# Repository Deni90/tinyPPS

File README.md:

## Description

TinyPPS is a pocket-sized programmable power supply built on the USB Power Delivery (PD) standard and the USB Programmable Power Supply (PPS) feature. It transforms a standard USB-C PD charger into a flexible bench-style power source by negotiating selectable output voltages and current limits directly with the charger.

## Key features

TinyPPS takes advantage of pin-compatible USB PD sink ICs (AP33772 and AP33772S), providing two feature sets within a single firmware, depending on the selected IC:

| Feature | With AP33772s | With AP33772 |
| - | - | - |
| Supported PDO profiles | fixed PDO, PPS | fixed PDO, PPS |
| Output voltage range | 3.3 - 21V | 3.3 - 21V |
| Max output current* | 5A | 5A |
| PPS voltage step size | 100mV/Step | 20mV/Step |
| Programmable current limit | 250mA/Step | 50mA/Step |
| User-switchable output | ✅ | ✅ |
| Over Voltage Protection (OVP) | ✅ → Hard Reset and Auto Restart | ✅ → Auto Restart |
| Over Current Protection (OCP) | ✅ → Output Disable | ✅ → Auto Restart |
| Under Voltage Protection (UVP) | ✅ → Output Disable | ❌ |
| Over temperature protection (OTP)** | ✅ → Output Disable | ✅ → Output Disable |
| Short-Circuit Protection (SCP) | ✅ → Output Disable | ✅ → Output Disable |

**charger and cable dependent*

***OTP is set to 85°C*

Huge thank you to **[PCBWay](https://www.pcbway.com)** for sponsoring this project!

## Firmware

The firmware is written in C++ using the Raspberry Pi Pico SDK. No external dependencies are used.

Configuring the build using CMake:

```bash
cd firmware
cmake -G Ninja -S . -B build
```

Building the firmware:

```bash
cmake --build build
```

## Flashing

There are two options to flash RP2040:
1. Via USB by pressing the `BOOT` button during power on. On a PC a new virtual drive called `RPI-RP2` should appear. Then, drag and drop a *.uf2* file onto the drive.
2. Via SWD interface by attaching a debugger like Raspberry Pi Debug Probe to the "DBG" connector and then using OpenOCD.
    ```bash
    cmake --build build --target flash
    ```

## Hardware

Schematic and PCB are designed in KiCAD 10.

Key components:

- The device is based on the **RP2040** microcontroller and **AP33772(S)** USB PD sink controller.
- A **0.96 in 128×64 SSD1306 OLED** is added to display the UI.
- A **EC11** rotary encoder is added for user input.
- **INA226** is used for measuring current and voltage. *While AP33772s provides these features, INA226 gives more precise measurements.*
- **LM73100** replaces the back-to-back NMOS switch and provides short circuit protection.
- **74LVC1G08GW,125** single 2-input AND gate is used for output enable.

## Case

3D model is made with Autodesk Fusion 360.

The case is 3D printed with ABS so it can handle higher tempeatures.

## Resources

1. [Hardware design with RP2040](https://pip-assets.raspberrypi.com/categories/814-rp2040/documents/RP-008279-DS-1-hardware-design-with-rp2040.pdf?disposition=inline)
2. [AP33772S I2C USB PD Sink Controller EVB User Guide](https://www.diodes.com/assets/Evaluation-Boards/AP33772S-Sink-Controller-EVB-User-Guide.pdf)
3. [SSD1306](https://cdn-shop.adafruit.com/datasheets/SSD1306.pdf)
4. [INA226](https://www.ti.com/lit/ds/symlink/ina226.pdf?ts=1770072845830)

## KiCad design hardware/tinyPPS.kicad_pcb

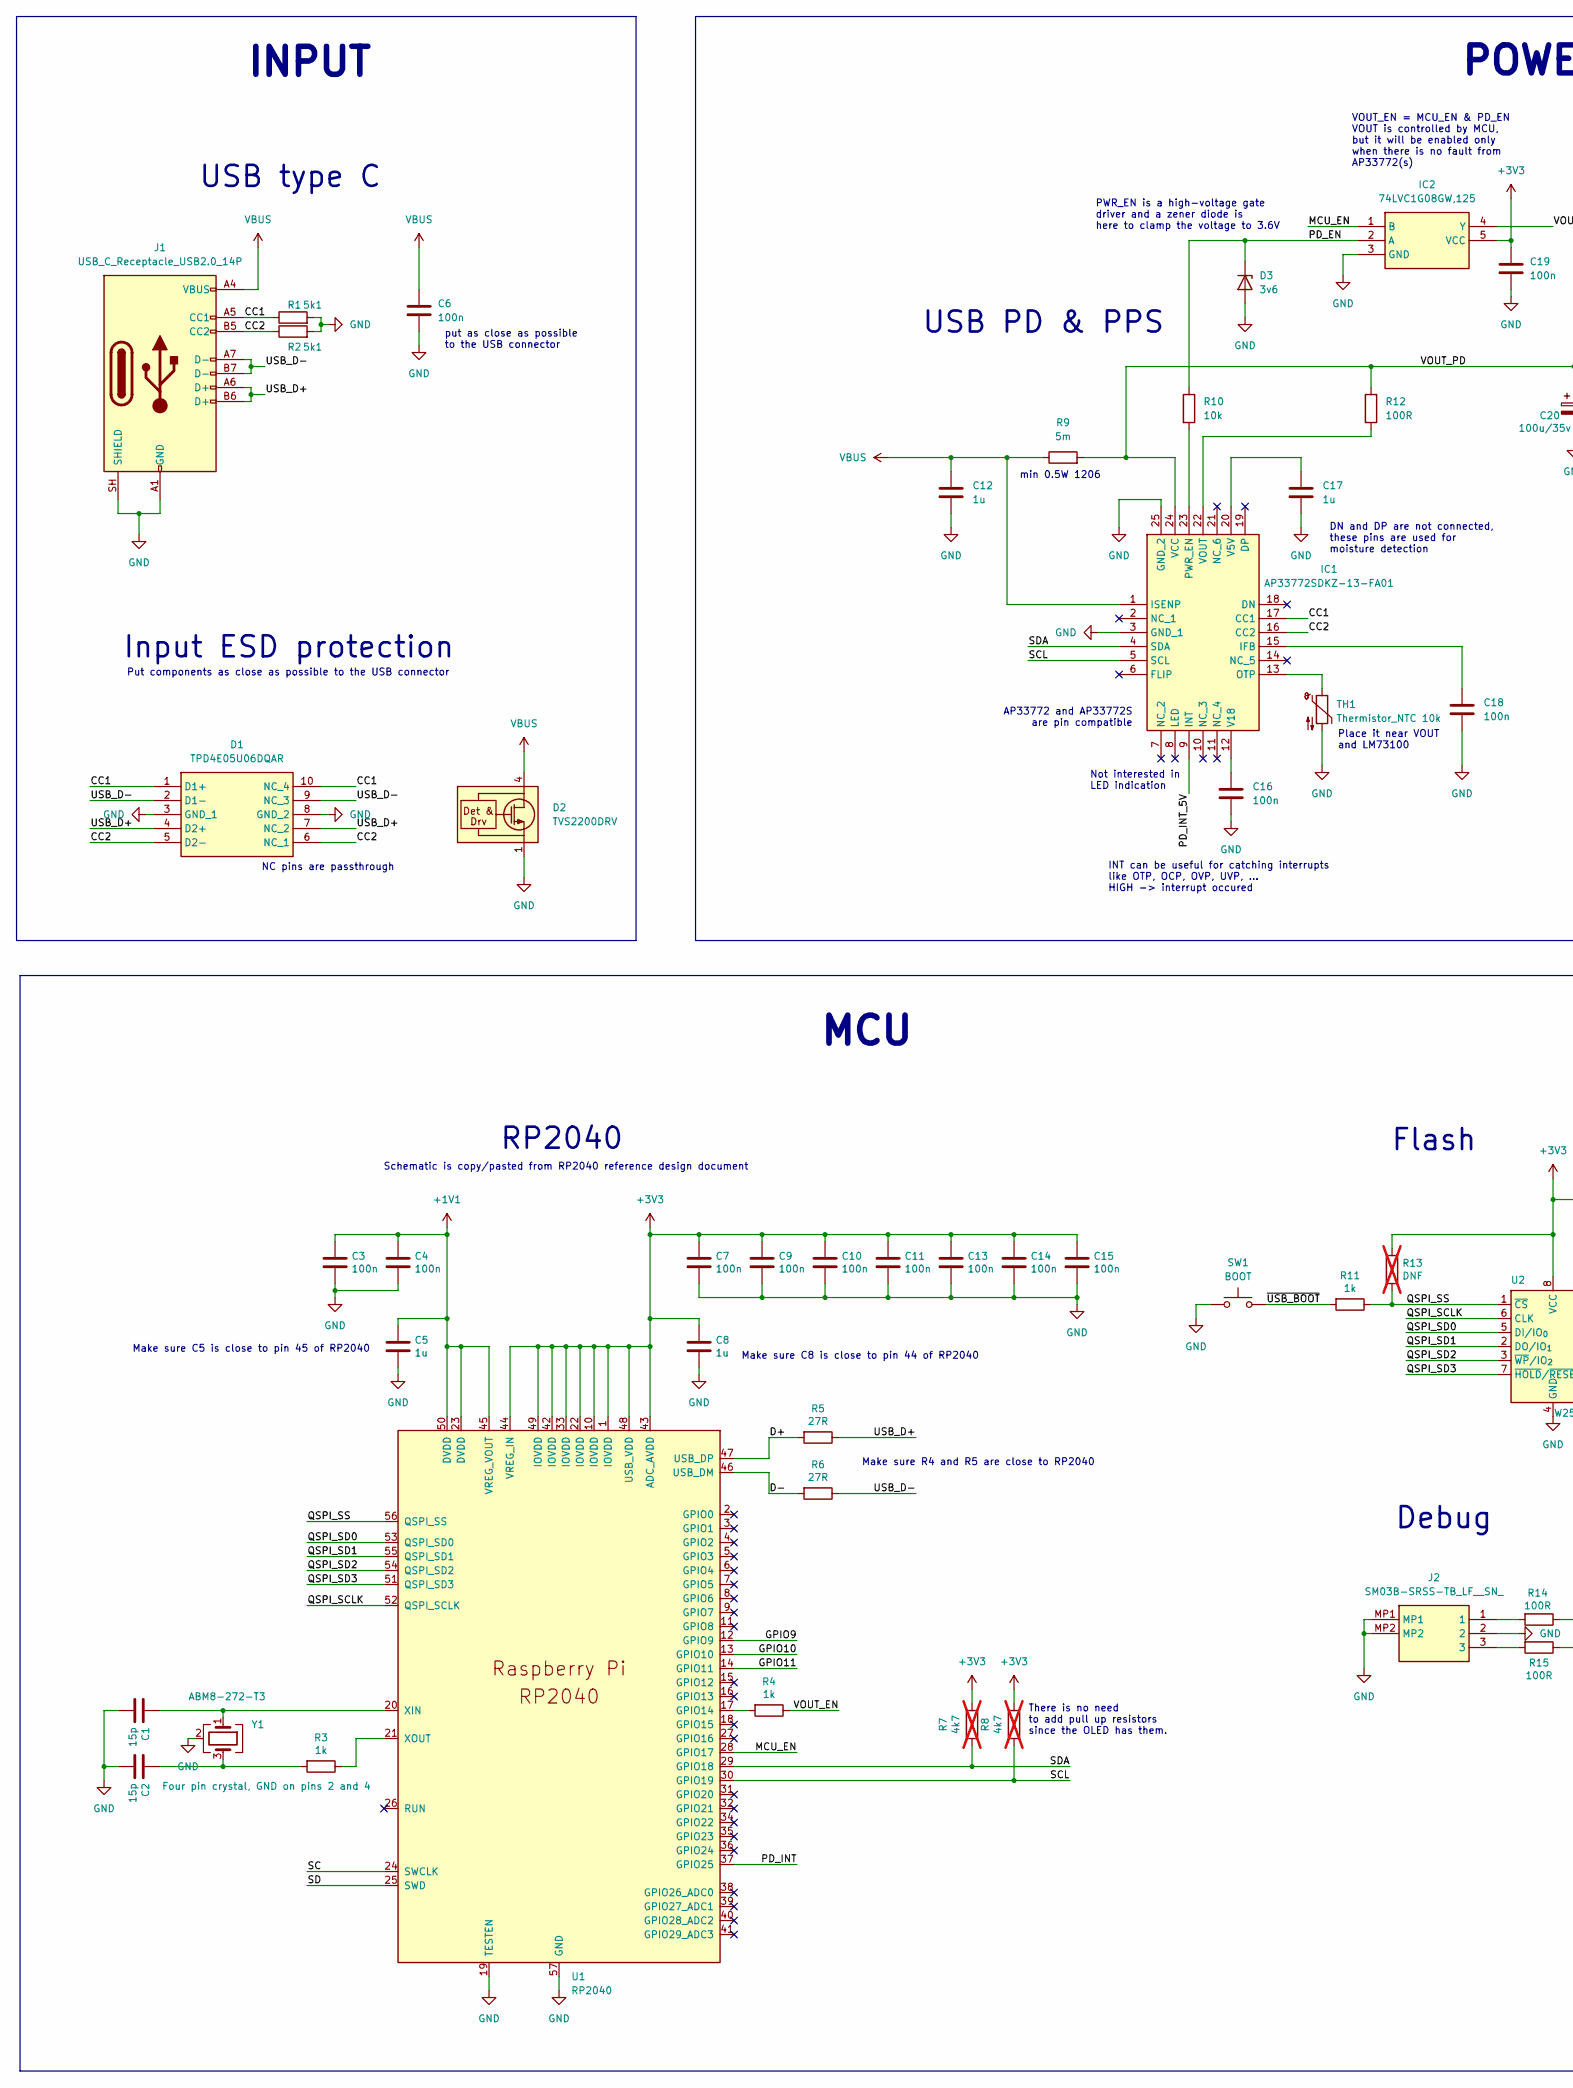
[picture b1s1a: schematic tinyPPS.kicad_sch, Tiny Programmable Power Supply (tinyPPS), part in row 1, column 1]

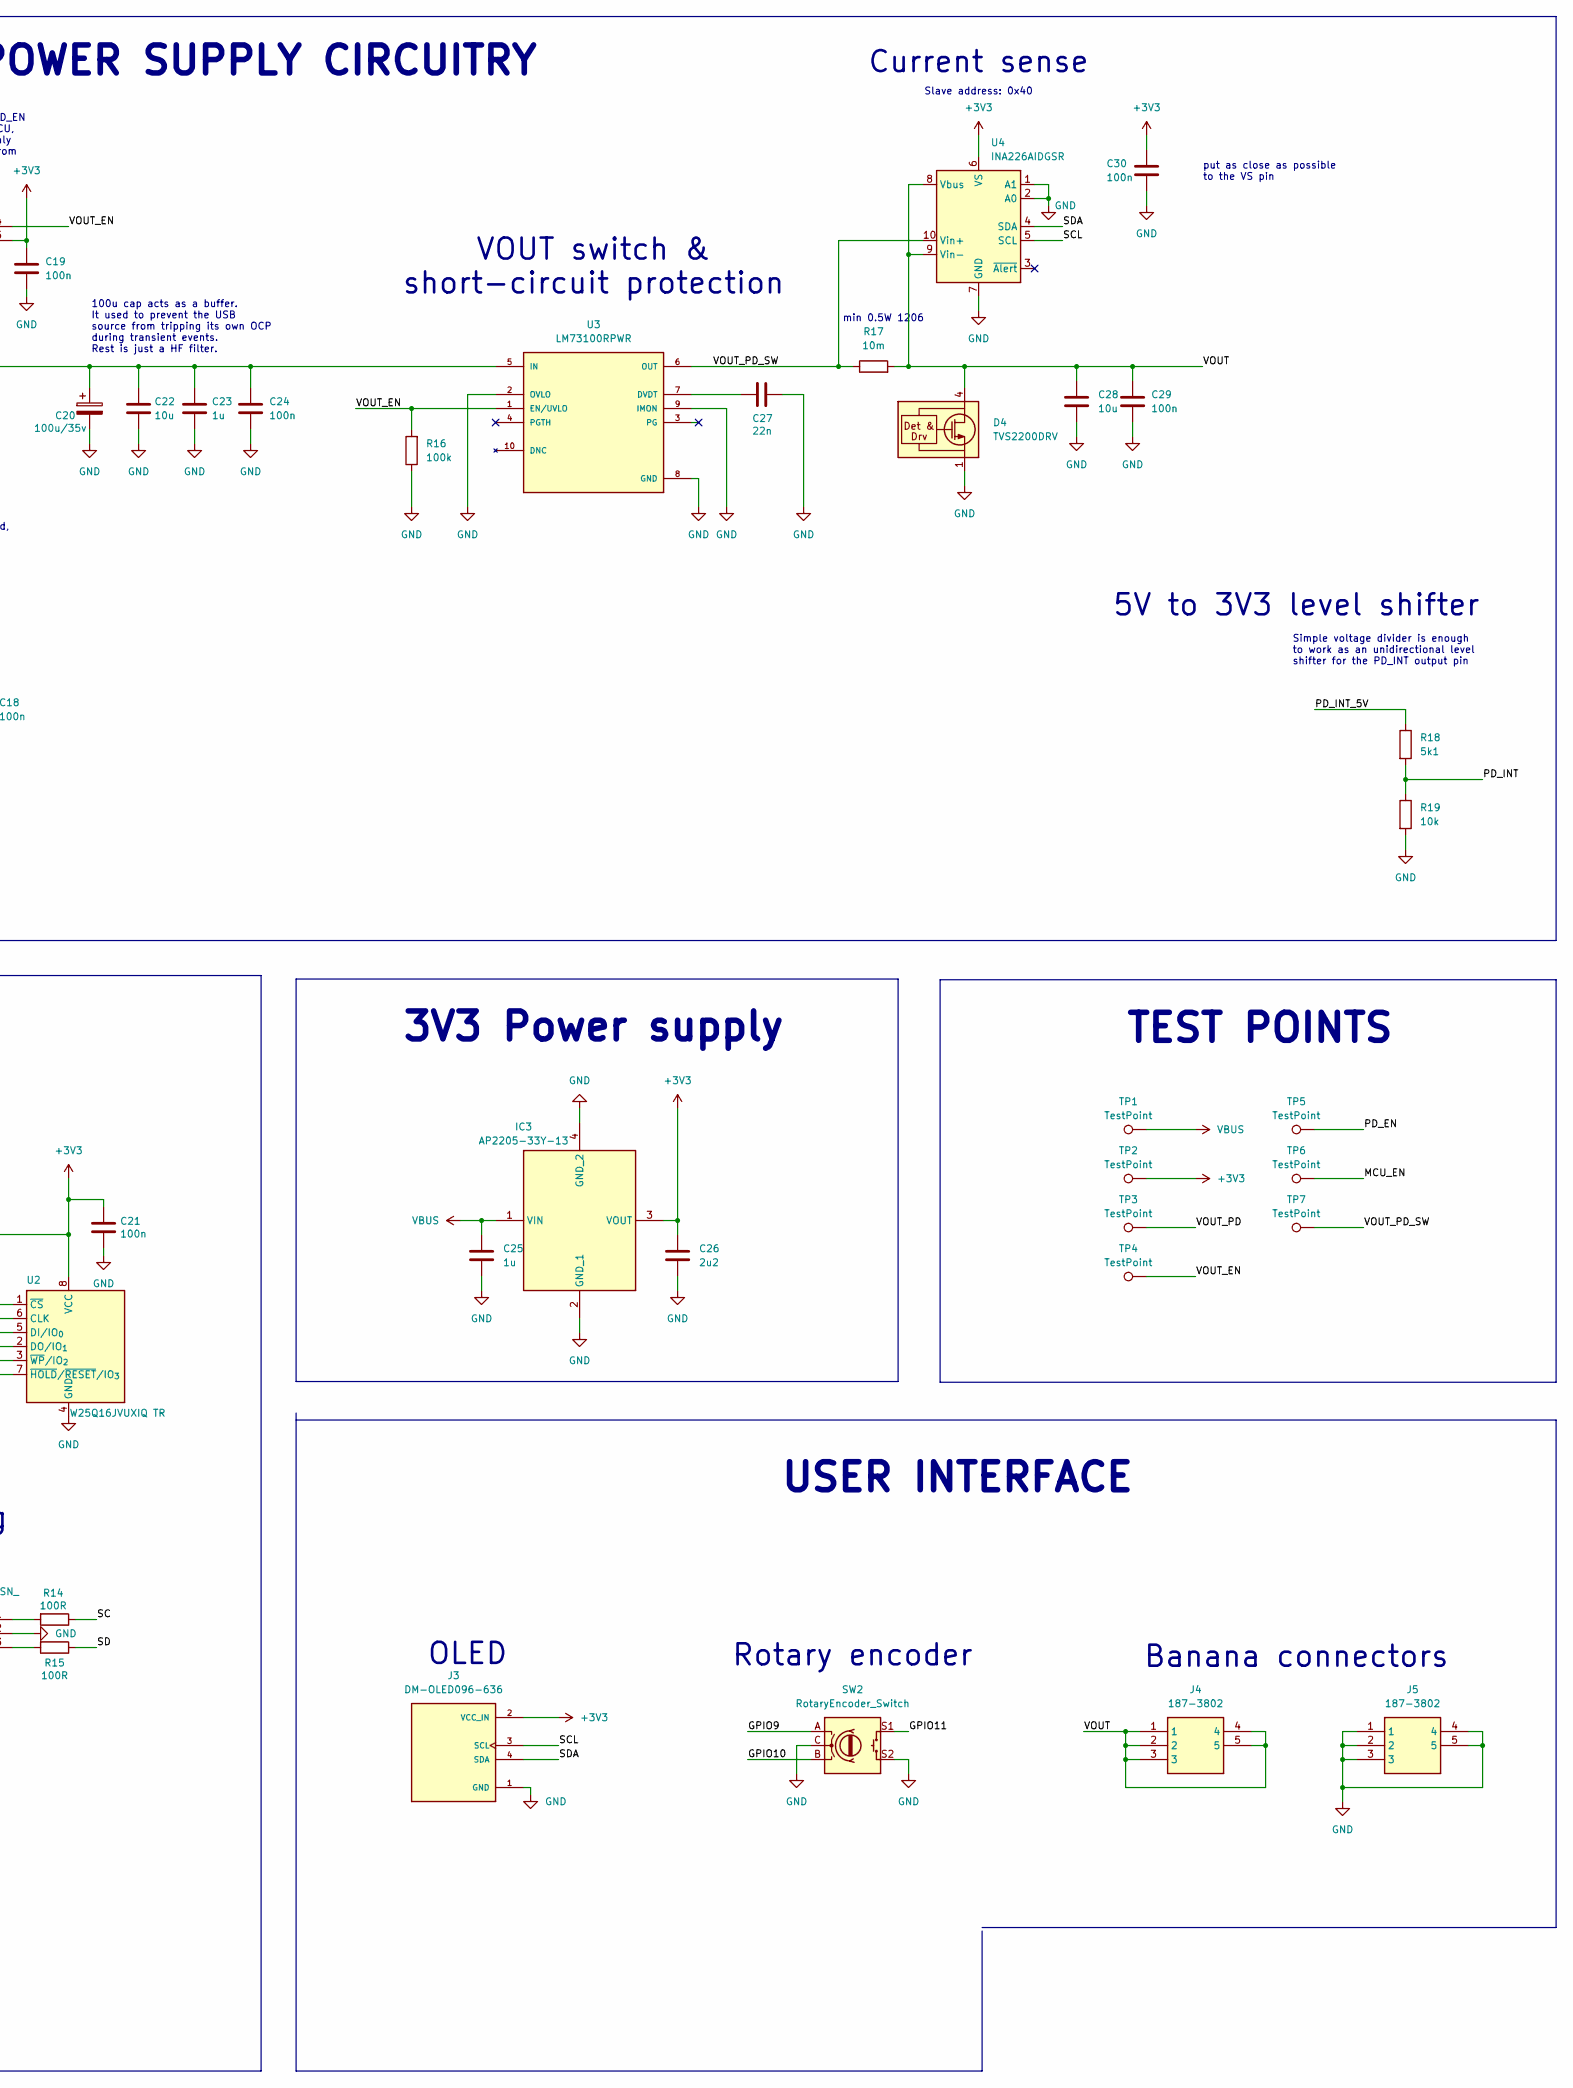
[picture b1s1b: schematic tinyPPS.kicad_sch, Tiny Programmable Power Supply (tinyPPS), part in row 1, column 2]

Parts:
C1, C2: 15p; C_0402_1005Metric
C3, C4, C6, C7, C9, C10, C11, C13, C14, C15, C16, C18, C19, C21, C24, C29, C30: 100n; C_0402_1005Metric
C5, C8, C12, C17, C25: 1u; C_0402_1005Metric
C20: 100u/35v; CP_Elec_6.3x7.7
C22, C28: 10u; C_0805_2012Metric
C23: 1u; C_0805_2012Metric
C26: 2u2; C_0402_1005Metric
C27: 22n; C_0402_1005Metric
D1: TPD4E05U06DQAR; DQA_R-PUSON-N10_; Mouser Part Number 595-TPD4E05U06DQAR
D2, D4: TVS2200DRV; WSON-6-1EP_2x2mm_P0.65mm_EP1x1.6mm
D3: 3v6; D_SOD-323
IC1: AP33772SDKZ-13-FA01; AP33772SDKZ13FA01; Mouser Part Number 621-P33772SDKZ13FA01
IC2: 74LVC1G08GW,125; SOT65P210X110-5N; Mouser Part Number 771-74LVC1G08GW-G
IC3: AP2205-33Y-13; 2DB1132R13; Mouser Part Number 621-AP2205-33Y-13
J1: USB_C_Receptacle_USB2.0_14P; USB_C_Receptacle_GCT_USB4105-xx-A_16P_TopMnt_Horizontal
J2: SM03B-SRSS-TB_LF__SN_; SM03BSRSSTBLFSN; Mouser Part Number N/A
J3: DM-OLED096-636; MODULE_DM-OLED096-636; PARTREV 2018-09-10
J4, J5: 187-3802; 1873802; Manufacturer_Part_Number 187-3802
R1, R2, R18: 5k1; R_0402_1005Metric
R3, R4, R11: 1k; R_0402_1005Metric
R5, R6: 27R; R_0402_1005Metric
R7, R8: 4k7; R_0402_1005Metric; not fitted
R9: 5m; R_1206_3216Metric
R10, R19: 10k; R_0402_1005Metric
R12, R14, R15: 100R; R_0402_1005Metric
R13: DNF; R_0402_1005Metric; not fitted
R16: 100k; R_0402_1005Metric
R17: 10m; R_1206_3216Metric
SW1: BOOT; SW_3x4mm
SW2: RotaryEncoder_Switch; EC11 horizontal
TH1: Thermistor_NTC 10k; R_0402_1005Metric
TP1, TP2, TP3, TP4, TP5, TP6, TP7: TestPoint; TestPoint_Pad_D1.0mm
U1: RP2040; RP2040-QFN-56
U2: W25Q16JVUXIQ TR; Winbond_USON-8-1EP_3x2mm_P0.5mm_EP0.2x1.6mm
U3: LM73100RPWR; IC_LM73100RPWR; PARTREV 08/2019
U4: INA226AIDGSR; TSSOP-10_3x3mm_P0.5mm
Y1: ABM8-272-T3; Crystal_SMD_3225-4Pin_3.2x2.5mm

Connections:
+1V1: C3.1, C4.1, C5.1, U1.23 (DVDD), U1.45 (VREG_VOUT), U1.50 (DVDD)
+3V3: C7.1, C8.1, C9.1, C10.1, C11.1, C13.1, C14.1, C15.1, C19.1, C21.1, C26.1, C30.1, IC2.5 (VCC), IC3.3 (VOUT), J3.2 (VCC_IN), R7.1, R8.1, R13.1, TP2.1 (1_1), U1.1 (IOVDD), U1.10 (IOVDD), U1.22 (IOVDD), U1.33 (IOVDD), U1.42 (IOVDD), U1.43 (ADC_AVDD), U1.44 (VREG_IN), U1.48 (USB_VDD), U1.49 (IOVDD), U2.8 (VCC), U4.6 (VS)
/CC1: D1.1 (D1+), D1.10 (NC_4), IC1.17 (CC1), J1.A5 (CC1), R1.1
/CC2: D1.5 (D2-), D1.6 (NC_1), IC1.16 (CC2), J1.B5 (CC2), R2.1
/D+: R5.2, U1.47 (USB_DP)
/D-: R6.2, U1.46 (USB_DM)
/GPIO9: SW2.A, U1.12 (GPIO9)
/GPIO10: SW2.B, U1.13 (GPIO10)
/GPIO11: SW2.S1, U1.14 (GPIO11)
/MCU_EN: IC2.1 (B), TP6.1 (1_1), U1.28 (GPIO17)
/PD_EN: D3.1 (K), IC2.2 (A), R10.1, TP5.1 (1_1)
/PD_INT: R18.2, R19.1, U1.37 (GPIO25)
/PD_INT_5V: IC1.9 (INT), R18.1
/QSPI_SCLK: U1.52 (QSPI_SCLK), U2.6 (CLK)
/QSPI_SD0: U1.53 (QSPI_SD0), U2.5 (DI/IO_{0})
/QSPI_SD1: U1.55 (QSPI_SD1), U2.2 (DO/IO_{1})
/QSPI_SD2: U1.54 (QSPI_SD2), U2.3 (~WP/IO_{2})
/QSPI_SD3: U1.51 (QSPI_SD3), U2.7 (~HOLD/~RESET/IO_{3})
/QSPI_SS: R11.1, R13.2, U1.56 (QSPI_SS), U2.1 (~CS)
/SC: R14.1, U1.24 (SWCLK)
/SCL: IC1.5 (SCL), J3.3 (SCL), R8.2, U1.30 (GPIO19), U4.5 (SCL)
/SD: R15.1, U1.25 (SWD)
/SDA: IC1.4 (SDA), J3.4 (SDA), R7.2, U1.29 (GPIO18), U4.4 (SDA)
/USB_D+: D1.4 (D2+), D1.7 (NC_2), J1.A6 (D+), J1.B6 (D+), R5.1
/USB_D-: D1.2 (D1-), D1.9 (NC_3), J1.A7 (D-), J1.B7 (D-), R6.1
/VOUT: C28.1, C29.1, D4.4 (IN), D4.5 (IN), D4.6 (IN), J4.1, J4.2, J4.3, J4.4, J4.5, R17.2, U4.8 (Vbus), U4.9 (Vin-)
/VOUT_EN: IC2.4 (Y), R4.1, R16.2, TP4.1 (1_1), U3.1 (EN/UVLO)
/VOUT_PD: C20.1, C22.1, C23.1, C24.1, IC1.24 (VCC), R9.2, R12.2, TP3.1 (1_1), U3.5 (IN)
/VOUT_PD_SW: R17.1, TP7.1 (1_1), U3.6 (OUT), U4.10 (Vin+)
/~USB_BOOT: R11.2, SW1.2
GND: C1.2, C2.2, C3.2, C4.2, C5.2, C6.2, C7.2, C8.2, C9.2, C10.2, C11.2, C12.2, C13.2, C14.2, C15.2, C16.2, C17.2, C18.2, C19.2, C20.2, C21.2, C22.2, C23.2, C24.2, C25.2, C26.2, C27.2, C28.2, C29.2, C30.2, D1.3 (GND_1), D1.8 (GND_2), D2.1 (GND), D2.2 (GND), D2.3 (GND), D2.7 (GND), D3.2 (A), D4.1 (GND), D4.2 (GND), D4.3 (GND), D4.7 (GND), IC1.3 (GND_1), IC1.25 (GND_2), IC2.3 (GND), IC3.2 (GND_1), IC3.4 (GND_2), J1.A1 (GND), J1.A12 (GND), J1.B1 (GND), J1.B12 (GND), J1.SH (SHIELD), J2.2, J2.MP1, J2.MP2, J3.1 (GND), J5.1, J5.2, J5.3, J5.4, J5.5, R1.2, R2.2, R16.1, R19.2, SW1.1, SW2.C, SW2.S2, TH1.2, U1.19 (TESTEN), U1.57 (GND), U2.4 (GND), U3.2 (OVLO), U3.8 (GND), U3.9 (IMON), U4.1 (A1), U4.2 (A0), U4.7 (GND), Y1.2 (G), Y1.4 (G)
unnamed: C2.1, R3.2, Y1.3
unnamed: C18.1, IC1.15 (IFB)
unnamed: IC1.13 (OTP), TH1.1
unnamed: IC1.23 (PWR_EN), R10.2
unnamed: C17.1, IC1.20 (V5V)
unnamed: C16.1, IC1.12 (V18)
unnamed: IC1.22 (VOUT), R12.1
unnamed: J2.1, R14.2
unnamed: J2.3, R15.2
unnamed: R4.2, U1.17 (GPIO14)
unnamed: C1.1, U1.20 (XIN), Y1.1
unnamed: R3.1, U1.21 (XOUT)
unnamed: C27.1, U3.7 (DVDT)
VBUS: C6.1, C12.1, C25.1, D2.4 (IN), D2.5 (IN), D2.6 (IN), IC1.1 (ISENP), IC3.1 (VIN), J1.A4 (VBUS), J1.A9 (VBUS), J1.B4 (VBUS), J1.B9 (VBUS), R9.1, TP1.1 (1_1)

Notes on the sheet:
100u cap acts as a buffer. It used to prevent the USB source from tripping its own OCP during transient events. Rest is just a HF filter.
There is no need to add pull up resistors since the OLED has them.
AP33772 and AP33772S are pin compatible
min 0.5W 1206
MCU
Not interested in LED indication
VOUT_EN = MCU_EN & PD_EN VOUT is controlled by MCU, but it will be enabled only when there is no fault from AP33772(s)
DN and DP are not connected, these pins are used for moisture detection
INPUT
Debug
put as close as possible to the USB connector
Input ESD protection
VOUT switch & short-circuit protection
Banana connectors
OLED
Slave address: 0x40
USB PD & PPS
Place it near VOUT and LM73100
Make sure R4 and R5 are close to RP2040
Flash
3V3 Power supply
INT can be useful for catching interrupts like OTP, OCP, OVP, UVP, ... HIGH -> interrupt occured
Make sure C5 is close to pin 45 of RP2040
Schematic is copy/pasted from RP2040 reference design document
put as close as possible to the VS pin
Make sure C8 is close to pin 44 of RP2040
USER INTERFACE
NC pins are passthrough
RP2040
Current sense
Rotary encoder
POWER SUPPLY CIRCUITRY
TEST POINTS
PWR_EN is a high-voltage gate driver and a zener diode is here to clamp the voltage to 3.6V
5V to 3V3 level shifter
USB type C
Simple voltage divider is enough to work as an unidirectional level shifter for the PD_INT output pin
Put components as close as possible to the USB connector

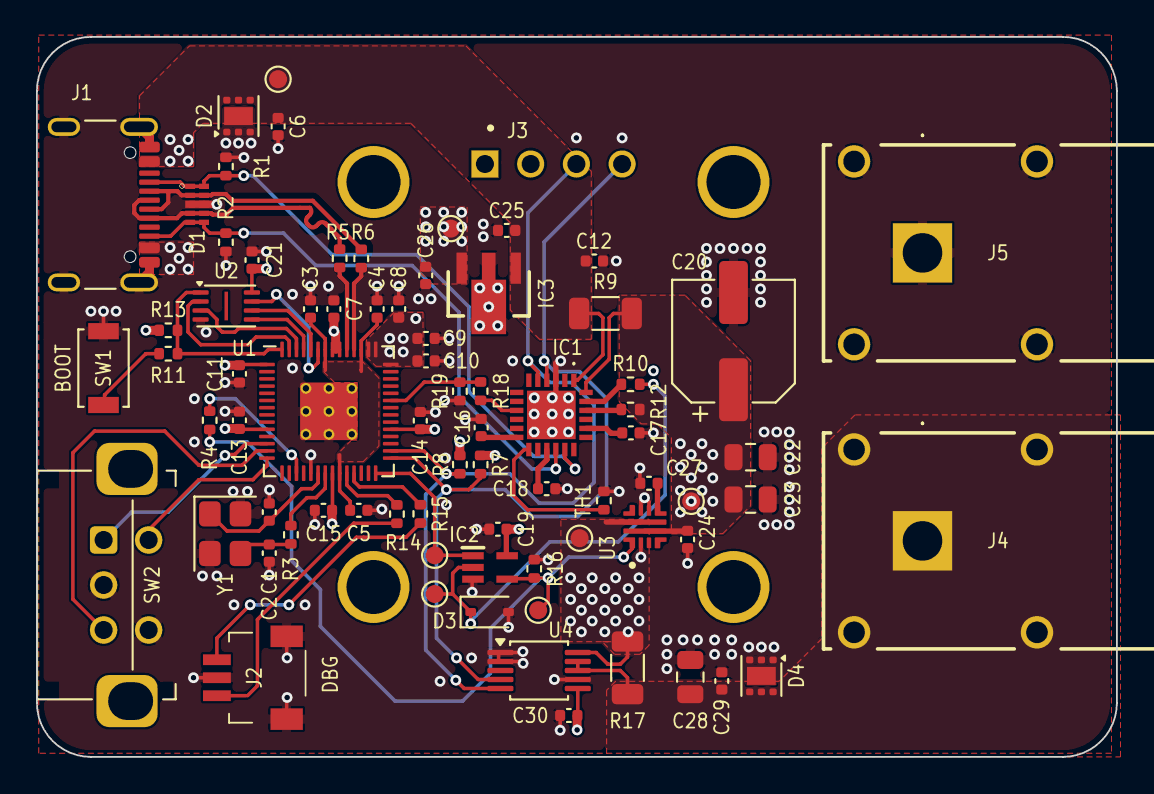
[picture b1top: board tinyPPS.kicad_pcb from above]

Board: 4 copper layers, 60.0 x 40.0 mm, 76 parts (0 on the bottom side), 45 nets.

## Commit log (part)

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2025-05-25 Implement a basic TinyPPS GUI layout and control
    - Implement OLED display driver
    - Implement rotary encoder driver
    - Implement main menu and main screens
    - Handle rotary encoder states
2025-06-03 Add schematic & PCB
2025-08-05 Update function names in ssd1306 to match the coding style
2025-08-11 Remove LED connection and update PD_INT level shifter
2025-08-12 Use back-to-back N MOS switch with common source
2025-08-12 Replace led indicator with mode
2025-08-13 Update project name in CMake
2025-08-13 Extend TinyPPS with initialize function
2025-08-18 Change rotary encoder to a horizontal type
    - Re-route the PCB
    - Make PCB with smaller (60mm)
2025-08-23 Update PCB routing - use +3v3 and GND planes
2025-08-29 Change PCB size to 60x40mm and update INA226 circuit
2025-12-03 Change footprint for flash to WSON-8 6x5mm and re-route the PCB
2026-01-21 Use rp2040, update GPIOs and INA226 shunt value to match PCB
2026-01-21 rotary_encoder: Move init to a separate function
2026-01-21 rp_imp: Move i2c initialization to separate function
2026-01-21 Show loading screen at startup
2026-01-24 Fix reading current from INA226
    - Remove output filterfing from INA266, cause it may not be correctly
    implemented.
2026-01-25 Update menu and loading screens to use simply "PDO" as term
2026-01-25 Read and show the number of PDOs from AP33772s
    - Add an app33772s module used for the driver code
    - Define register objects (Status, Mask, System, SrcPdo and PdReqMsg)
    - Implement a basic API for getting status, setting NTC values, control the
    ouput enable NMOS switch and read PDOs from a USB power source.
2026-01-26 Move config* to utils folder
2026-01-28 Move PdoType enum to Ap33772s class
2026-01-28 Show menu only if enabled and when the output is turned off
2026-01-28 Implement PDO selection
    - Extend Ap33772s with setVselMin function to enable voltages bellow 5V.
    - Extend Ap33772s with getPdo funtion for retrieving PDO at specified index.
    - Extend Ap33772s with setPdoOutput function for selecting PDO with output
    voltage and current.
    - Update config to use Pdo structure.
    - Integrate PDO selection into main module.
2026-01-29 Ap33772s: Add helper functions for i2c handling
2026-01-29 MainScreen: Convert temperature member to int
2026-01-29 Disable warnings caused by using std::format
2026-01-29 Fix showing default target V for a when there is no PDO available
    The issue is fixed by setting voltage_min to 5000 in Pdo's constructor.
2026-01-29 MainScreen: Calculate the x position for target current/voltage strings
2026-01-30 Ap33772s: Expose getStatus and setMask functions to public API
2026-01-30 Hal: rename pin_iface to gpio_iface
2026-01-30 Hal: Simplify initialization of gpio pins
    - Add Direction and Pull enums
    - Move GPIO init to a configure function
2026-01-30 Hal: Move timer stuff to HAL and implement a PicoRepeatingTimer
2026-01-31 TinyPPS: Move output_enable under TinyPPS class
2026-01-31 Gui: Add logo to loading screen
2026-02-02 Gpio: Add interrupt handling to the API
2026-02-02 Handle faults triggered by the PD_INT interrupt
    - Attach an interrupt to PD_INT pin
    - Disable output if fault is raised
2026-02-07 TinyPPS: Add init state to State enum
    - Move readPDO to handleInitState function
2026-02-07 Ap33772s: Remove non-working code from getPdo
2026-02-07 Gui: MainScreen - use "LIMIT" text for current
2026-03-26 Update README fix values for output voltage range
2026-04-01 Gui: MenuScreen - Fix showing all menu items properly
    Decrease max_menu_size by one to match the layout height. This solves the
    problem of showing the 7th menu item on the next page.
2026-04-27 TinyPPS: Remove i2c handling from ISR
    ISR now only sets an interrupt flag. I2C read is handled in main state.
2026-04-27 Ap33772s: Move i2c address to classes public section
2026-04-27 TinyPPS: Declare m_is_fault_detected as volatile
2026-04-27 HAL: Extend HAL with IPdSink for USB PD Sink control
    IPdSink class provides a generic API for USB Power Delivery Sink hardware. This
    addition opens the possibility to support different types of PD controllers
    without modifying code in the main module.
2026-04-27 Ap33772s: Refactor the module by implementing the IPdSink interface
    Refactor Ap33772s to use IPdSink interface and update other modules to use
    objects from IPdSink.
2026-04-27 PCB: Assign colors to nets to improve readability
2026-04-27 Hardware: Switch to 4-layer board setup
    Schematic:
    - Add TVS diodes to input and output
    - Support both AP33772 and AP33772s
    - Replace back-to-back NMOS swith with a single LM73100. AP33772(s) has a
    PWR_EN pin that is used as a gate driver for the NMOS switch. Voltage levels
    of the PWR_EN can be greater than the maximum rating of 6.5V for LM73100.
2026-04-27 TinyPPS: Add support for AP33772
    - Implement an AP33772 module based on IPdSink
    - Integrate AP33772 to TinyPPS
    - Extend probe function to detect AP33772 by default and fallback to AP33772s
    if it is not detected
2026-05-24 Hal: Modernize code and address clang-tidy warnings
    - Use a trailing return type for functions
    - Rename cb parameter to callback
2026-05-24 PicoHal:: Fix clang-tidy warnings
    - Modernize C++ code
    - Use better variable/argument names
2026-05-24 Ina226: Fix clang-tidy warnings
    - Modernize C++ code
2026-05-24 RotaryEncoder: Fix clang-tidy warnings
    - Modernize C++ code
2026-05-25 Ap33772(s): Fix clang-tidy warnings
    - Modernize C++ code
2026-05-25 TinyPPS: Modernize C++ code
2026-05-25 RotaryEncoder: Refactor Handle() function
    - Move static variables from Handle() to class members to enable proper
    handling across multiple objects
    - Simplify button debounce logic
2026-05-26 TinyPPS: Refactor Menu state handling
    - Introduce MenuStateData struct for storing state data
    - Remove unnecessary while loop from the state handler function
    - Use switch/case instead of if/else to improve readability
2026-05-26 TinyPPS: Refactor Main state handling
    - Introduce MainStateData struct for storing state data
    - Move creation of default config in case of no profiles detected to init state
    handler
    - Remove unnecessary while loop from the state handler function
    - Use m_system_time for calculating time based operations
2026-05-26 RoratyEncoder: Rename Handle function to handle
2026-05-27 TinyPPS: Refactor menu and main state handlers
    - Move MenuScreen to be part of MenuStateData
    - Handle clearing encoder state at one place instead of clearing in every
    encoder state inside switch/case
2026-05-27 Update project version and add target for flashing
    - Change version to 2.0
    - Format file
    - Add a custom target "flash" to flash firmware via openocd
2026-05-27 TinyPPS: Extent menu and main state handlers with data argument
2026-05-27 RotaryEncoder: Use references instead of pointers
2026-05-27 Ssd1306: Use reference for i2c instead of pointer
2026-05-27 Ina226: Use reference for i2c instead of pointer
2026-05-27 TinyPPS: Use std::reference_wrapper for m_pd_sink
    - During initialization check is AP33772 connected to i2c bus. If not, fallback
    to AP33772s.
2026-05-29 Move hw initialization to main
    - Create a HardwareContext struct to hold references to hardware interfaces
    - Use HardwareContext in TinyPPS module
    - Define and initialize peripherals in main
2026-05-29 CMakeLists.txt: Update config to work with the v2 PCB
    - Set PICO_BOARD to "none"
    - Disable exceptions and RTTI (not related to v2 PCB)
2026-05-29 TinyPPS: Move content from readPdos() to handleInitState
2026-05-29 TinyPPS: Update "EN" icon based on vout_status(VOUT_EN) input
2026-05-30 TinyPPS: Use brace initialization of struct members
2026-05-30 TinyPPS: Make a fixed 250mA/mV big step
    - Remove magic numbers for calculating big steps for voltage and current when
    incrementing/decrementing values
2026-05-30 TinyPPS: Move periodic stuff out of switch/case in handleMainState
2026-05-30 TinyPPS: Refactor handleMainState
    - Combine handling rot_inc and rot_dec states of rotary encoder
    - Fix switching back to menu state -> prevent going back if there is only one
    PDO available
2026-05-30 MainScreen: Set voltage/current labels based on supply type
2026-05-30 Rename TinyPPS to StateMachine
2026-05-31 StateMachine: Switch to event driven state machine
    - Create event structs
    - Extend MenuScreen with selectNextMenuItem and selectPreviousMenuItem functions.
    - Refactor state machine to use event driven state machine.
    - Create an render() function for updating the oled display within the state machine.
    - Move interrupt handling and timer initialization to main.
    - Set newpdo_* to mask to enable interrupt when new PDOs are received.
2026-05-31 Ignore AVS PDOs, since the HW is not supporting more than 21V
2026-06-01 Screen: Use std::string_view in printString functions
2026-06-02 StateMachine: Handle when the LM73100 turns off the output due to a short circuit
    - Introduce a ramp-up period when enabling the output.
    - Turn off the output only if the low voltage is detected for the configured
    ammount of times.
2026-06-04 Hardware: Add a comment about how to choose the correct shunt
    - AP33772 and AP33772S are using different shunts
2026-06-04 Ssd1306: Reduce contrast of the OLED
2026-06-04 Add 3D model of the case to the repo
2026-06-08 Update README with new features and add new images
    - Update key features section with a table describing features based on
    selected PD sink controller IC (AP33772 or AP33772s).
    - Add instructions for configuring, building and flashing the project.
    - Extend README with a new section: Case
2026-06-10 StateMachine: Rename target_current/voltage to user_current/voltage
2026-06-13 StateMachine: Refactor output enable handling
    - Create setOutputEnable function as part of MainState for controlling the
    output enable pin and updating the screen at one place.
    - Handle vout_status, the output of the AND gate, via interrupt and propagate
    the event to the state machine.
2026-06-14 HAL: Update II2c to use std::span
    - Update all modules using i2c to use the new API
2026-06-14 Screen: Remove hardcoded screen dimensions
    - Instead of using hardcoded screen dimension, they are now get from the oled
    screen. Screen no longer has a static std::array, instead a std::span. The
    frame buffer is now created in main module and then the Screen is initialized
    via static initializer.
2026-06-15 PicoGpio: Move gpio_init from constructor to configure()
2026-06-15 Ssd1306: Fill m_old_fb with 0xff to fix startup glitches
    Setting m_old_fb array values to non-zero value fixes the dirty page tracking.
    As a result, the whole screen updates during the first display() call.
2026-06-15 IGpio, PicoGpio: Improve const-correctness
    Mark methods as const since they do not modify internal class state.
2026-06-17 HAL: Refactor GPIO to use static polymorphism
    - Replace IGpio virtual interface with a compile-time GpioPin concept
    - Move Direction, Pull, Edge enums and IrqCallback under the hal::gpio
    namespace
    - Create hardware_config.hpp to handle aliases for concrete hardware classes
    - Update modules to consume the new GpioPin type alias
    - Mark driver constructors constexpr to force pin data into the .rodata section
2026-06-17 HAL: Refactor RepeatingTimer to use static polymorphism
    - Replace IRepeatingTimer virtual interface with a compile-time
    RepeatingTimer concept
    - Move Callback under the hal::timer namespace
2026-06-17 HardwareContext: Remove unused struct members
2026-06-17 Rename header files to *.hpp
2026-06-17 IPdSink: Use brace initializer for struct members
2026-06-17 CMakeLists.txt: Add -Wpedantic to CMAKE_CXX_FLAGS and fix warnings
    Fix warnings related to anonymous structs
2026-06-17 Main: Initialize hardware in a separate function
